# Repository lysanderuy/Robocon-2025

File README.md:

USC Robocon-2025 - Robotics Competition (Line Following)

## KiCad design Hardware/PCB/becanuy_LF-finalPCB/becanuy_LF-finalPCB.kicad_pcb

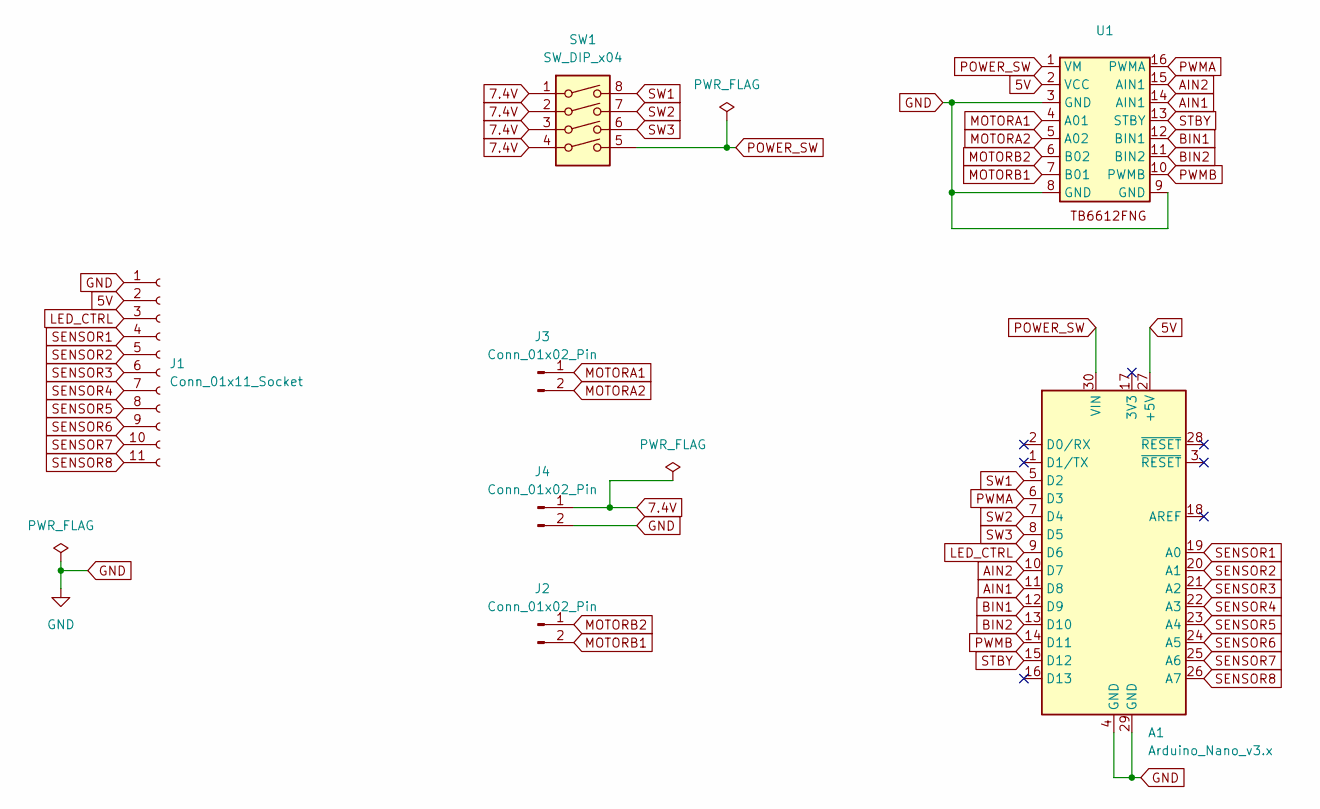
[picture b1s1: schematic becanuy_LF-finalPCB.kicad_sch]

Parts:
A1: Arduino_Nano_v3.x; Arduino_Nano
J1: Conn_01x11_Socket; PinHeader_1x11_P2.54mm_Vertical
J2, J3, J4: Conn_01x02_Pin; JST_XH_B2B-XH-A_1x02_P2.50mm_Vertical
SW1: SW_DIP_x04; SW_DIP_SPSTx04_Slide_9.78x12.34mm_W7.62mm_P2.54mm
U1: TB6612FNG

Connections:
5V: A1.27 (+5V), J1.2, U1.2 (VCC)
7.4V: J4.1, SW1.1, SW1.2, SW1.3, SW1.4
AIN1: A1.11 (D8), U1.14 (AIN1)
AIN2: A1.10 (D7), U1.15 (AIN1)
BIN1: A1.12 (D9), U1.12 (BIN1)
BIN2: A1.13 (D10), U1.11 (BIN2)
GND: A1.4 (GND), A1.29 (GND), J1.1, J4.2, U1.3 (GND), U1.8 (GND), U1.9 (GND)
LED_CTRL: A1.9 (D6), J1.3
MOTORA1: J3.1, U1.4 (A01)
MOTORA2: J3.2, U1.5 (A02)
MOTORB1: J2.2, U1.7 (B01)
MOTORB2: J2.1, U1.6 (B02)
POWER_SW: A1.30 (VIN), SW1.5, U1.1 (VM)
PWMA: A1.6 (D3), U1.16 (PWMA)
PWMB: A1.14 (D11), U1.10 (PWMB)
SENSOR1: A1.19 (A0), J1.4
SENSOR2: A1.20 (A1), J1.5
SENSOR3: A1.21 (A2), J1.6
SENSOR4: A1.22 (A3), J1.7
SENSOR5: A1.23 (A4), J1.8
SENSOR6: A1.24 (A5), J1.9
SENSOR7: A1.25 (A6), J1.10
SENSOR8: A1.26 (A7), J1.11
STBY: A1.15 (D12), U1.13 (STBY)
SW1: A1.5 (D2), SW1.8
SW2: A1.7 (D4), SW1.7
SW3: A1.8 (D5), SW1.6

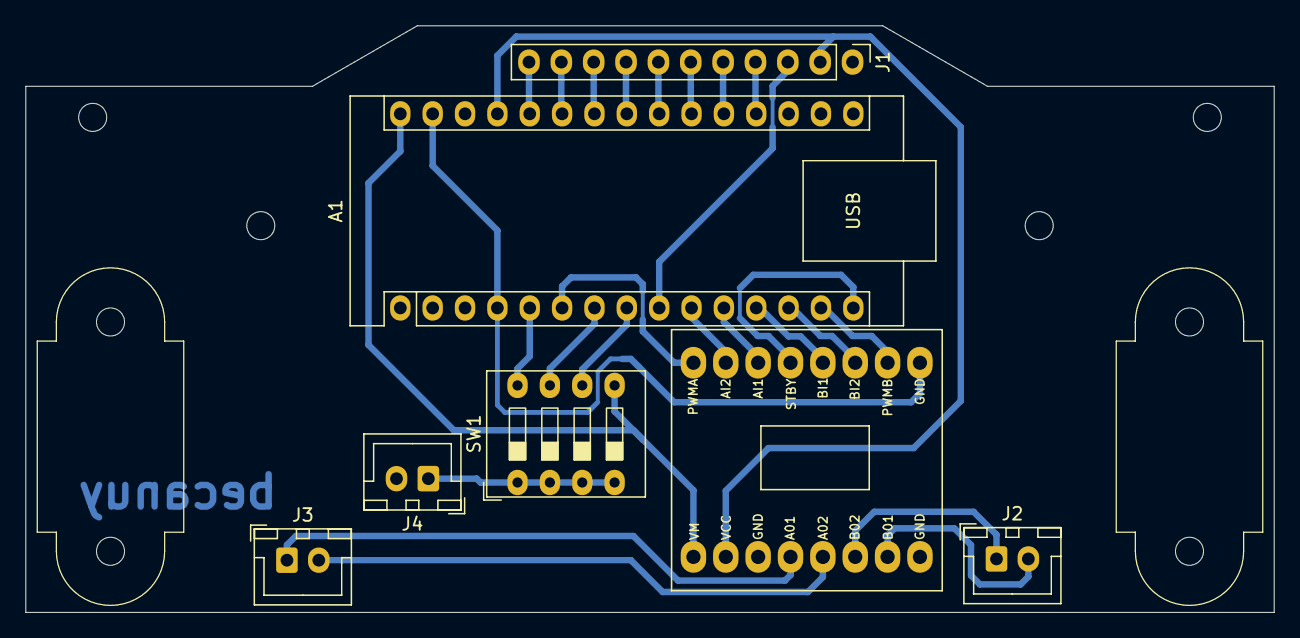
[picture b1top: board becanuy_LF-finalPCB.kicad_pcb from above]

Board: 2 copper layers, 98.0 x 46.0 mm, 7 parts (0 on the bottom side), 27 nets.

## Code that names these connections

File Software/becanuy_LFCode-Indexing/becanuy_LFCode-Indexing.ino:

#include <QTRSensors.h>
#include <SparkFun_TB6612.h>

// Calibration variables
const int ledPin = LED_BUILTIN;
int ledState = LOW;
int threshold = 0;
int thresholdAllowance = 250;
String direction = " ";
int BASE_PWM = 200;

// QTR 8A pin assignments
#define SENSOR8 A7
#define SENSOR7 A6
#define SENSOR6 A5
#define SENSOR5 A4
#define SENSOR4 A3
#define SENSOR3 A2
#define SENSOR2 A1
#define SENSOR1 A0
#define LED_CTRL 6

// TB6612FNG pin assignments
#define PWMA 3
#define PWMB 11
#define AIN2 7
#define AIN1 8
#define BIN1 9
#define BIN2 10
#define STBY 12

// Motor setup
Motor leftMotor = Motor(AIN1, AIN2, PWMA, 1, STBY);
Motor rightMotor = Motor(BIN1, BIN2, PWMB, 1, STBY);

// Sensor setup
const uint8_t sensorArray[8] = { SENSOR8, SENSOR7, SENSOR6, SENSOR5, SENSOR4, SENSOR3, SENSOR2, SENSOR1 };
uint16_t sensorValues[8];
QTRSensors qtr;
int SensorCount = 8;

void setup() {
  Serial.begin(9600);

  qtr.setTypeAnalog();
  qtr.setSensorPins(sensorArray, SensorCount);

  pinMode(ledPin, OUTPUT);
  pinMode(LED_CTRL, OUTPUT);
  digitalWrite(LED_CTRL, HIGH);
  delay(5);

  noCalibration();
}

void loop() {
  qtr.read(sensorValues);

  followLine1();
}

//======================================vvvLINE FOLLOWING FUNCTIONSvvv======================================//
void followLine1() {
  int indexDarkest = 0;  // Initial index of sensor detecting darkest line

  // Keeping track of the sensor with darkest reading
  for (int i = 0; i < 8; i++) {
    if (sensorValues[i] > sensorValues[indexDarkest])
      indexDarkest = i;
  }

  if (sensorValues[indexDarkest] > threshold) {
    switch (indexDarkest) {
      case 0:
        runMotors(0, 1);
        direction = "LLLL";
        break;
      case 1:
        runMotors(.2, 1);
        direction = "LLL";
        break;
      case 2:
        runMotors(.65, 1);
        direction = "LL";
        break;
      case 3:
        runMotors(.88, 1);
        direction = "L";
        break;
      case 4:
        runMotors(1, .88);
        direction = "R";
        break;
      case 5:
        runMotors(1, .65);
        direction = "RR";
        break;
      case 6:
        runMotors(1, .2);
        direction = "RRR";
        break;
      case 7:
        runMotors(1, 0);
        direction = "RRRR";
        break;
      default:
        break;
    }
  }
}
//======================================vvvLINE FOLLOWING FUNCTIONSvvv======================================//

//======================================vvvCALIBRATIONS FUNCTIONSvvv======================================//
void noCalibration() {
  stop();

  threshold = 200;

  runMotors(180, 180);
  delay(500);
}

void calibrateSensors() {
  stop();

  int numSamples = 10;
  int arrayThreshold[8] = { 0 };

  for (int j = 0; j < numSamples; j++) {
    qtr.read(sensorValues);
    for (int i = 0; i < 8; i++) {
      arrayThreshold[i] += sensorValues[i];
    }
    delay(50);
  }

  for (int i = 0; i < 8; i++) {
    arrayThreshold[i] /= numSamples;
  }

  int indexWhitest = 0;
  for (int i = 1; i < 8; i++) {
    if (arrayThreshold[i] < arrayThreshold[indexWhitest])
      indexWhitest = i;
  }

  threshold = arrayThreshold[indexWhitest] + thresholdAllowance;

  blinkLED();
}

void blinkLED() {
  for (int i = 0; i < 3; i++) {
    digitalWrite(ledPin, HIGH);
    delay(500);
    digitalWrite(ledPin, LOW);
    delay(500);
  }
}
//======================================^^^CALIBRATIONS FUNCTIONS^^^======================================//

//======================================vvvSENSOR FUNCTIONSvvv======================================//
void displayReadings(int* sensorReadings) {
  int val_8 = sensorReadings[0];
  int val_7 = sensorReadings[1];
  int val_6 = sensorReadings[2];
  int val_5 = sensorReadings[3];
  int val_4 = sensorReadings[4];
  int val_3 = sensorReadings[5];
  int val_2 = sensorReadings[6];
  int val_1 = sensorReadings[7];

  Serial.print("\t");
  Serial.print("8: ");
  Serial.print(val_8);
  Serial.print("\t");
  Serial.print("7: ");
  Serial.print(val_7);
  Serial.print("\t");
  Serial.print("6: ");
  Serial.print(val_6);
  Serial.print("\t");
  Serial.print("5: ");
  Serial.print(val_5);
  Serial.print("\t");
  Serial.print("4: ");
  Serial.print(val_4);
  Serial.print("\t");
  Serial.print("3: ");
  Serial.print(val_3);
  Serial.print("\t");
  Serial.print("2: ");
  Serial.print(val_2);
  Serial.print("\t");
  Serial.print("1: ");
  Serial.print(val_1);
  Serial.print("\t");

  Serial.print("\t");
  Serial.print(direction);

  Serial.println();
}
//======================================^^^SENSOR FUNCTIONS^^^======================================//

//======================================vvvCUSTOM MOTOR FUNCTIONSvvv======================================//
void runMotors(int left, int right) {
  leftMotor.drive(BASE_PWM * left);
  rightMotor.drive(BASE_PWM * right);
}

void stop() {
  leftMotor.drive(0);
  rightMotor.drive(0);
}

void spinRight(int speed) {
  leftMotor.drive(speed);
  rightMotor.drive(-1 * speed);
}

void spinLeft(int speed) {
  leftMotor.drive(-1 * speed);
  rightMotor.drive(speed);
}
//======================================^^^CUSTOM MOTOR FUNCTIONS^^^======================================//

//======================================vvvEMOTE FUNCTIONSvvv======================================//
void emoteOne() {
  runMotors(255, 255);
  delay(500);
  stop();
  delay(300);
  spinLeft(255);
  delay(225);
  stop();
  delay(300);

  runMotors(255, 255);
  delay(500);
  stop();
  delay(300);
  spinLeft(255);
  delay(225);
  stop();
  delay(300);

  runMotors(255, 255);
  delay(500);
  stop();
  delay(300);
  spinLeft(255);
  delay(225);
  stop();
  delay(300);

  runMotors(255, 255);
  delay(500);
  stop();
  delay(300);
  spinLeft(255);
  delay(225);
  stop();
  delay(300);
}
//======================================^^^EMOTE FUNCTIONS^^^======================================//

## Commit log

2025-03-31 Design 3D model for sensor mount and rack
2025-04-21 Update: Software and Hardware
2025-04-21 Update: Hardware & Software
2025-04-22 Create: Multiple LF Logic
2025-04-29 Add: final PID code with switching speed modes
2025-04-29 Add: Final PCB design and schematic
